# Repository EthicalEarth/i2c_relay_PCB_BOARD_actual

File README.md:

There is a PCB project to connect 8-relay module with i2c bus

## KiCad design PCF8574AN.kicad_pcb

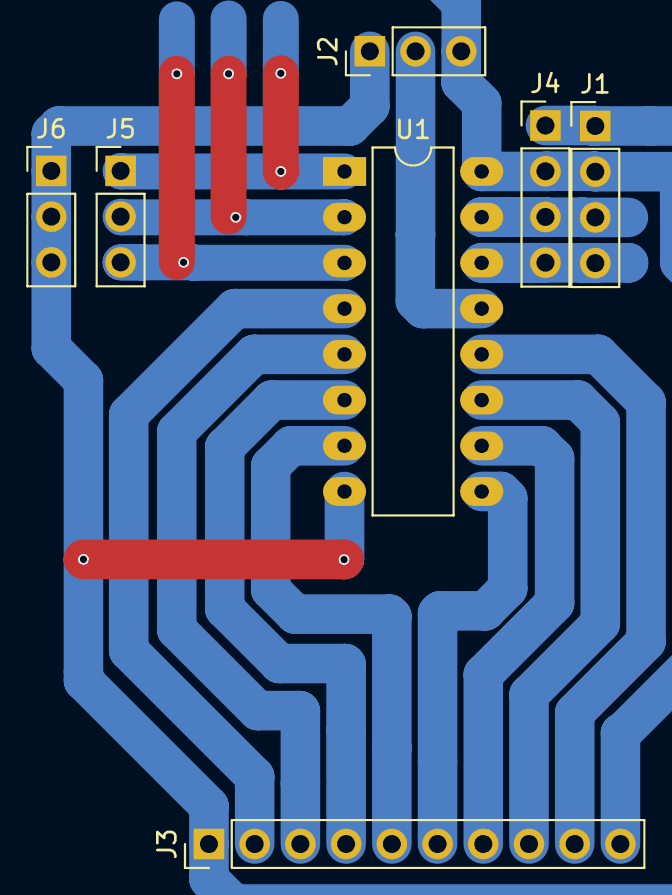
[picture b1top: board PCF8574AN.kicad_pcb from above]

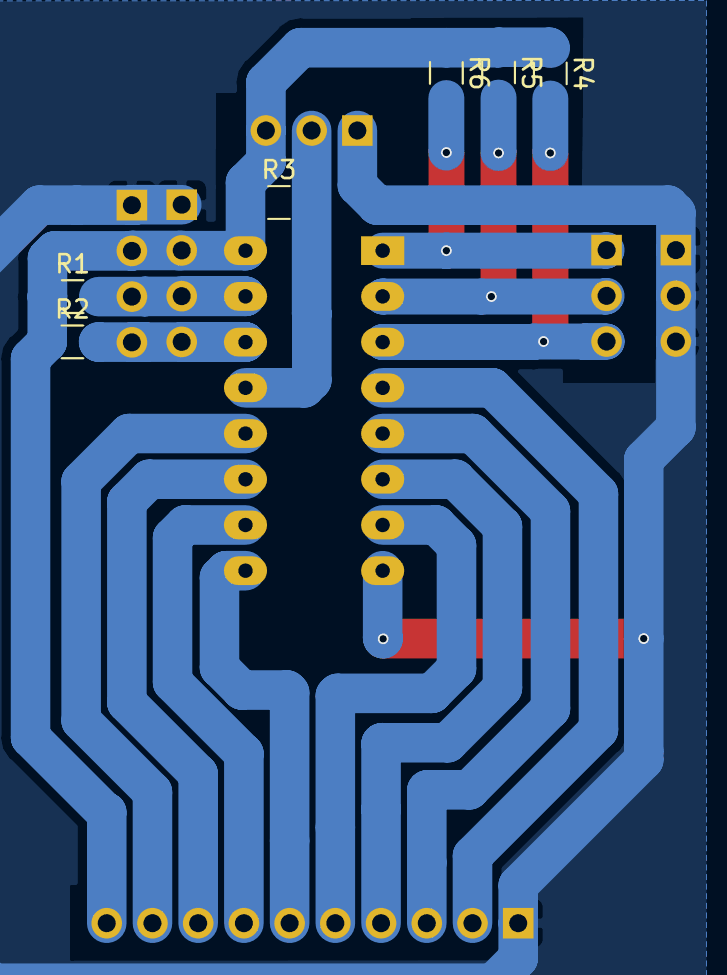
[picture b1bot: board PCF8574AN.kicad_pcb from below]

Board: 2 copper layers, 13 parts (6 on the bottom side), 16 nets.

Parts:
J1, J4: Conn_01x04_Male; PinHeader_1x04_P2.54mm_Vertical
J2, J5, J6: Conn_01x03_Male; PinHeader_1x03_P2.54mm_Vertical
J3: Conn_01x10_Male; PinHeader_1x10_P2.54mm_Vertical
R1, R2, R3, R4, R5, R6: R; R_1206_3216Metric
U1: PCF8574; DIP-16_W7.62mm_LongPads

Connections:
+5V: J1.2, J2.3, J3.10, J4.2, R1.1, R2.1, R3.1, R4.1, R5.1, R6.1, U1.16
GND: J1.1, J2.1, J3.1, J4.1, J6.1, J6.2, J6.3, U1.8
unnamed: J1.3, J4.3, R1.2, U1.15
unnamed: J1.4, J4.4, R2.2, U1.14
unnamed: J2.2, R3.2, U1.13
unnamed: J3.2, U1.4
unnamed: J3.3, U1.5
unnamed: J3.4, U1.6
unnamed: J3.5, U1.7
unnamed: J3.6, U1.9
unnamed: J3.7, U1.10
unnamed: J3.8, U1.11
unnamed: J3.9, U1.12
unnamed: J5.1, R6.2, U1.1
unnamed: J5.2, R5.2, U1.2
unnamed: J5.3, R4.2, U1.3

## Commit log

2018-07-28 Init
2018-09-29 Migrate project to new Kicad version. Adding headers for change address of chip PCF8574.
2021-08-25 Discription's update
    There is a PCB project to connect 8-relay module with i2c bus.
